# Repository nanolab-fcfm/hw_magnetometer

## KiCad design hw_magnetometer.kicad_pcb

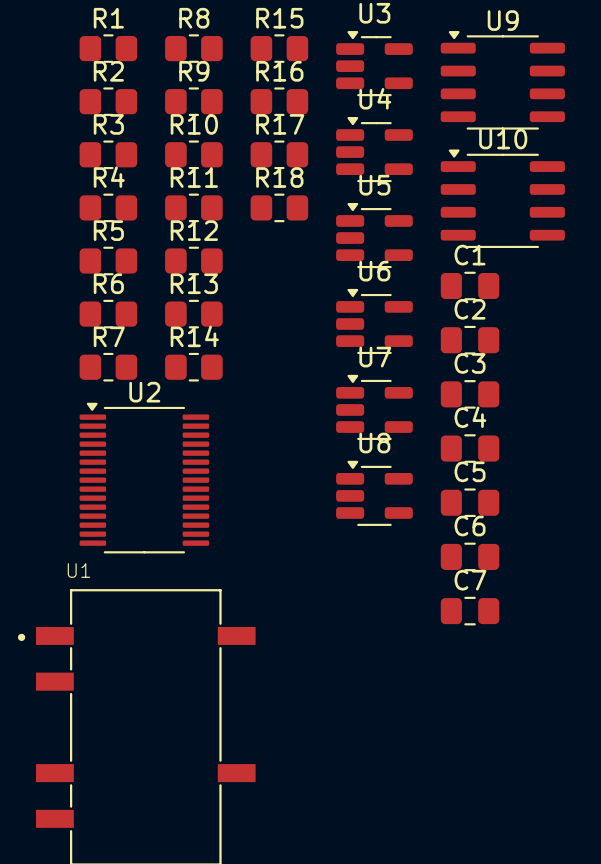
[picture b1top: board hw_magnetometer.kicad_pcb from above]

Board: 2 copper layers, 35 parts (0 on the bottom side), 21 nets, no tracks yet.

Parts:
C1, C2, C3: 4u7; C_0805_2012Metric_Pad1.18x1.45mm_HandSolder
C4, C5, C6: 1u; C_0805_2012Metric_Pad1.18x1.45mm_HandSolder
C7: 10u; C_0805_2012Metric_Pad1.18x1.45mm_HandSolder
R1, R7, R13: 243; R_0805_2012Metric_Pad1.20x1.40mm_HandSolder
R2, R8, R14: 20k; R_0805_2012Metric_Pad1.20x1.40mm_HandSolder
R3, R4, R5, R6, R9, R10, R11, R12, R15, R16, R17, R18: 1k; R_0805_2012Metric_Pad1.20x1.40mm_HandSolder
U1: PES1-S5-D5-M; CONV_PES1-S5-D24-M
U2: ADS7951QDBTRQ1; TSSOP-30_4.4x7.8mm_P0.5mm
U3, U4, U5, U6, U7, U8: SOT-23-5_HandSoldering
U9, U10: REF200AU; SOIC-8_3.9x4.9mm_P1.27mm

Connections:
+2V5: C7.1, R3.2, R9.2, R15.2
+3V3: C4.1, U2.28 (+VBD)
+5V: C3.1, C5.1, C6.1, U1.7 (+VO), U2.21 (+VA_2), U3.5 (V+), U4.5 (V+), U5.5 (V+), U6.5 (V+), U7.5 (V+), U8.5 (V+), U9.7, U9.8, U10.8
-5V: C2.1, U1.5 (-VO), U3.2 (V-), U4.2 (V-), U5.2 (V-), U6.2 (V-), U7.2 (V-), U8.2 (V-), U9.6 (S), U10.6 (S)
/MAGNETOMETER/AMP_1: R2.1, R4.2, U3.1
/MAGNETOMETER/AMP_2: R8.1, R10.2, U5.1
/MAGNETOMETER/AMP_3: R14.1, R16.2, U7.1
/MAGNETOMETER/COND_1: R6.1, U2.20 (CH0), U4.1
/MAGNETOMETER/COND_2: R12.1, U2.17 (CH3), U6.1
/MAGNETOMETER/COND_3: R18.1, U2.12 (CH6), U8.1
/MAGNETOMETER/Vin: C1.1, U1.2 (VIN)
GND: C1.2, C2.2, C3.2, C4.2, C5.2, C6.2, C7.2, R1.2, R5.2, R7.2, R11.2, R13.2, R17.2, U1.1 (GND), U1.4 (0V), U2.10 (AGND_2), U2.22 (AGND_3), U2.27 (BDGND)
unnamed: R1.1, R2.2, U3.4 (-)
unnamed: R3.1, R4.1, U4.3 (+)
unnamed: R5.1, R6.2, U4.4 (-)
unnamed: R7.1, R8.2, U5.4 (-)
unnamed: R9.1, R10.1, U6.3 (+)
unnamed: R11.1, R12.2, U6.4 (-)
unnamed: R13.1, R14.2, U7.4 (-)
unnamed: R15.1, R16.1, U8.3 (+)
unnamed: R17.1, R18.2, U8.4 (-)

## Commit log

2024-06-11 general structure
2024-09-30 reformatted schematic structure
2024-09-30 updated root page, sym and fp libs
2024-09-30 magnetometer design
